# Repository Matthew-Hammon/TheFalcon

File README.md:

# The Falcon

This is a project that was inspired by ZSA's Moonlander and Voyager split keyboards. I loved how they looked and with my move to a keyboard-driven workflow, I decided that I needed to make the move. I started second-guessing myself when I saw the price, as I was a student, and I came to the realisation that I had the skills to design one.

## Features
* 36 keys per split
* Serial communication between keyboards
* USB2.0 with USB-C connectors
* Voltage protection for hot plugging
* 4 layer PCB
* RGB lighting (see the note)
* QMK compatible
* Compatible with both [Gateron Low Profile 2.0](https://www.gateron.co/products/gateron-low-profile-mechanical-switch-set) (KS-33) and [Gateron G Pro switches](https://www.gateron.co/products/gateron-switch-set)

> [!NOTE]
> I have not been able to get the RGB lighting to work. I have checked the PCB schematic and nothing stands out as the error but I could be wrong. I believe that the problem comes down to the firmware implementation and drivers.

### PCB
The PCB folder contains files for the left and right PCBs separately as well as a panelised version that combines them. The PCBs were designed by me with inspiration from other similar projects. Although four layers increase the production cost, they were intentionally kept to ensure proper signal integrity and return paths, especially due to the fast switching of multiple lines for RGB, PWM and the USB differential pair.

### Case
The SolidWorks folder contains all of the CAD files that I made for the case/switch panel. 
The folders ending with _Threaded are for the initial case designs when I had initial ideas of having the case CNCed. They have threaded pillars used for screwing the bottom plate into the top, with the top also housing the keyboard switches. 
The folders with _ScrewHoles contain a full CAD design for the case, with a bottom case being used along with M2.5 screws and hex standoffs to attach to the switch panel. The switch panel was made using FR-4 and placed alongside the PCB order. Two versions of this were made, one for 'normal' switches and an adjusted one for low-profile switches.

### Parts
All of the parts can be found in the PartsList.xlsx file. The file is detailed and most of the parts have links to places I sourced them from at the time.
A bill of materials for the panel is found as 'bom.xlsx' with the parts positions in 'pos.xlsx'. These were formatted for JLCPCB and at the time they worked. I take no responsibility for anyone who uses them along with the panel for production and I HIGHLY encourage anyone using the files to double-check everything.

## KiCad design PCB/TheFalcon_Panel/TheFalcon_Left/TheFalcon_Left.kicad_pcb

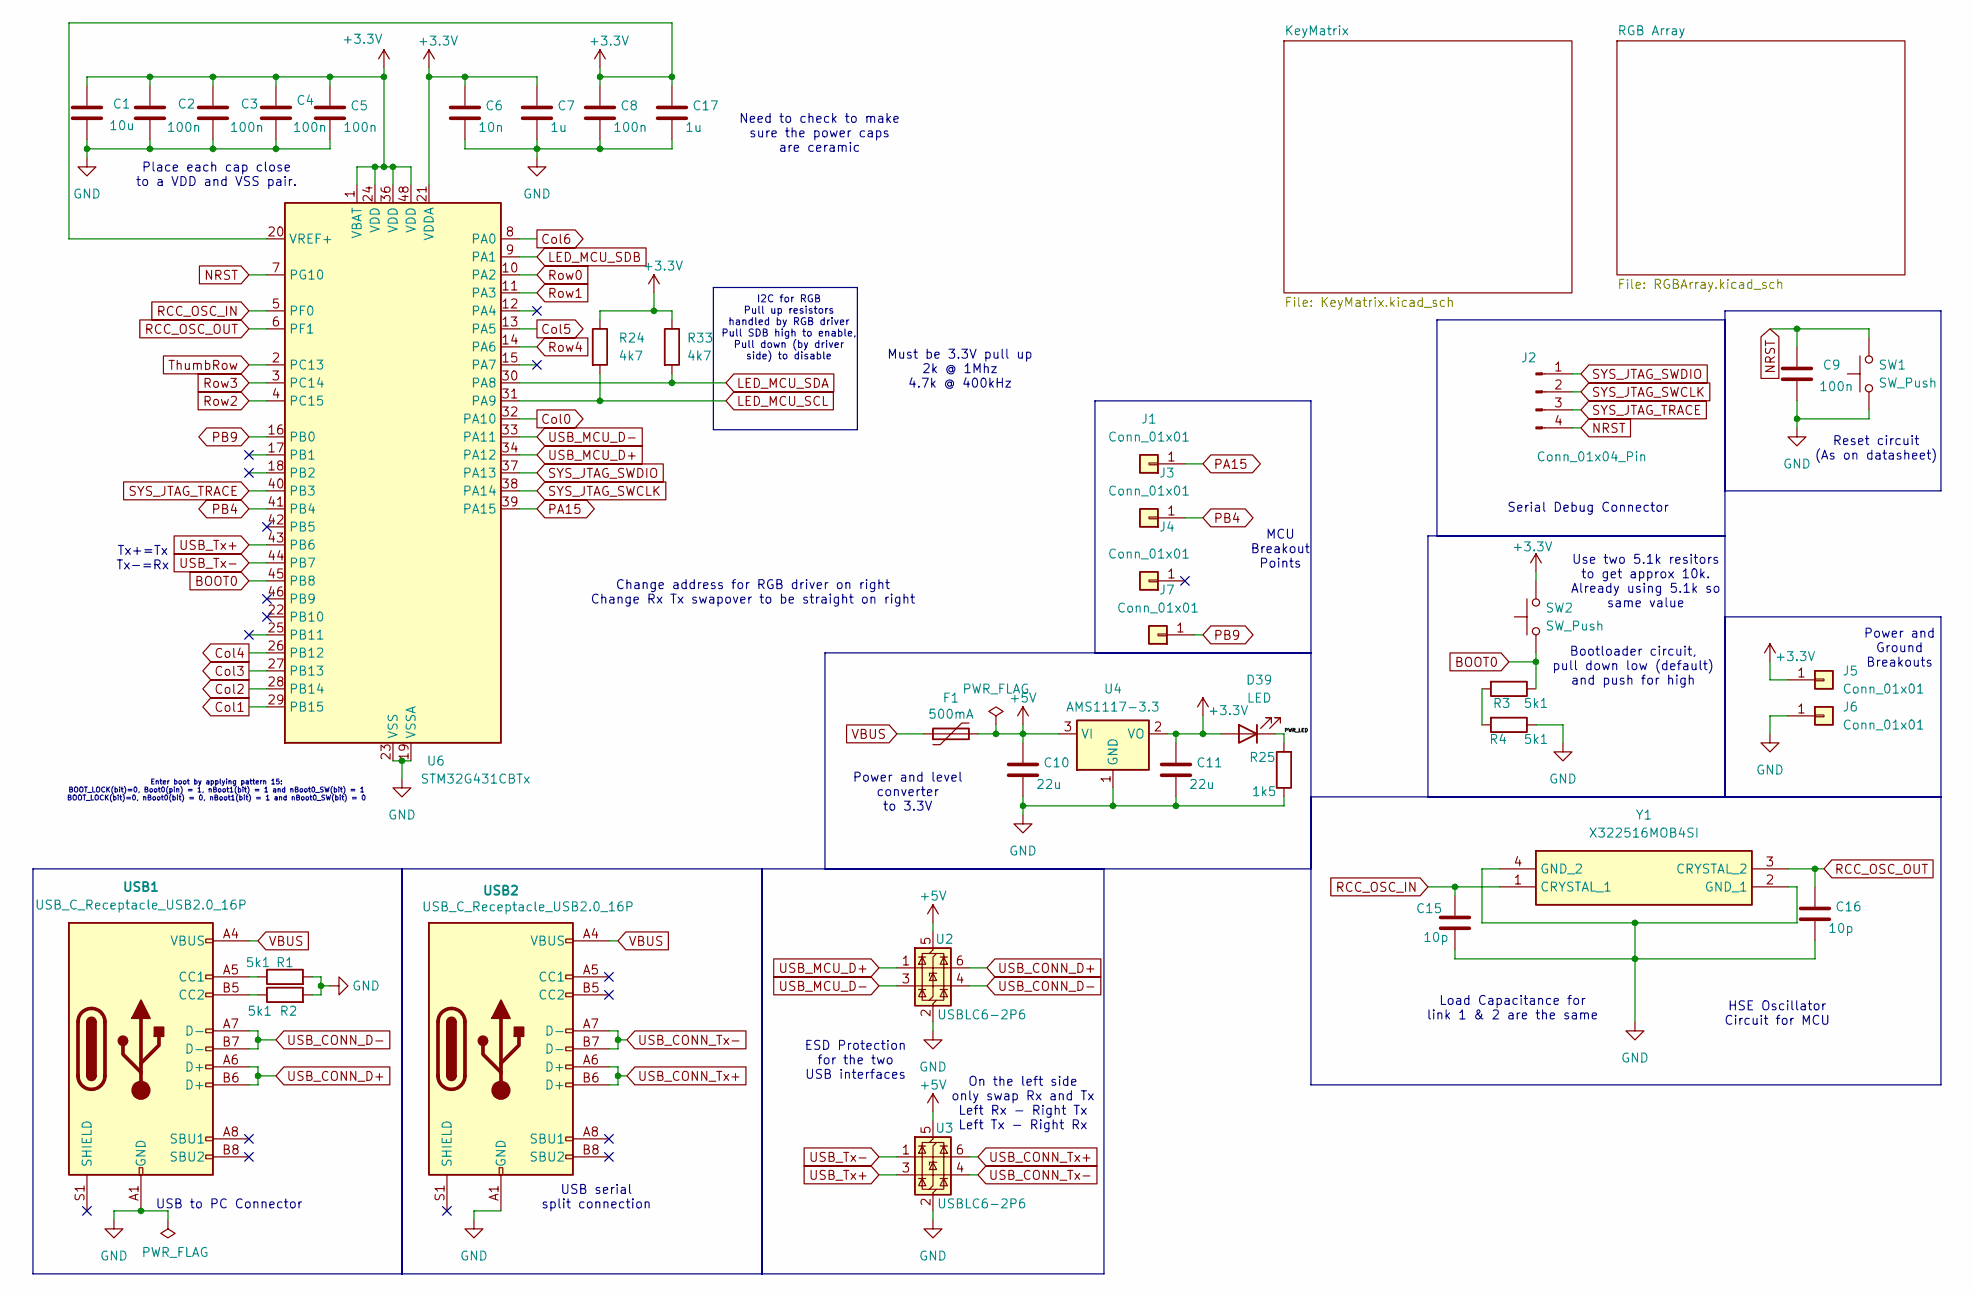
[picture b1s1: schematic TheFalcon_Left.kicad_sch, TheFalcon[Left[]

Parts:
C1: 10u; C_0805_2012Metric; LCSC Part Number C1713
C2, C3, C4, C5, C8, C9: 100n; C_0402_1005Metric; LCSC Part Number C1525
C6: 10n; C_0402_1005Metric; LCSC Part Number C1524
C7, C17: 1u; C_0603_1608Metric; LCSC Part Number C1592
C10, C11: 22u; C_1206_3216Metric; LCSC Part Number C1859
C15, C16: 10p; C_0402_1005Metric; LCSC Part Number C1545
D39: LED; LED_0805_2012Metric; LCSC Part Number C84260
F1: 500mA; Fuse_1206_3216Metric; LCSC Part Number C135336
J1, J3, J4, J5, J6, J7: Conn_01x01; SolderWire-0.1sqmm_1x01_D0.4mm_OD1mm
J2: Conn_01x04_Pin; SolderWire-1sqmm_1x04_P5.4mm_D1.4mm_OD2.7mm
R1, R2, R3, R4: 5k1; R_0603_1608Metric; LCSC Part Number C23067
R24, R33: 4k7; R_0603_1608Metric; LCSC Part Number C23162
R25: 1k5; R_0603_1608Metric; LCSC Part Number C22843
SW1, SW2: SW_Push; SPDT_Switch_KiCad_BasicComponent; LCSC Part Number C231329
U2, U3: USBLC6-2P6; SOT-666; LCSC Part Number C29780639
U4: AMS1117-3.3; SOT-223-3_TabPin2; LCSC Part Number C6186
U6: STM32G431CBTx; LQFP-48_7x7mm_P0.5mm; LCSC Part Number C529355
USB1, USB2: USB_C_Receptacle_USB2.0_16P; USB_C_Receptacle_G-Switch_GT-USB-7010ASV; LCSC Part Number C2988369
Y1: X322516MOB4SI; LCSC Part Number C12668

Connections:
+3.3V: C1.1, C2.1, C3.1, C4.1, C5.1, C6.1, C7.1, C8.1, C11.1, C17.1, D39.2 (A), J5.1, R24.1, R33.1, SW2.2, U4.2 (VO), U6.1 (VBAT), U6.20 (VREF+), U6.21 (VDDA), U6.24 (VDD), U6.36 (VDD), U6.48 (VDD)
+5V: C10.1, F1.2, U2.5 (VBUS), U3.5 (VBUS), U4.3 (VI); also elsewhere on the board
/PWR_LED: D39.1 (K), R25.2
BOOT0: R3.1, SW2.1, U6.45 (PB8)
Col0: U6.32 (PA10); also elsewhere on the board
Col1: U6.29 (PB15); also elsewhere on the board
Col2: U6.28 (PB14); also elsewhere on the board
Col3: U6.27 (PB13); also elsewhere on the board
Col4: U6.26 (PB12); also elsewhere on the board
Col5: U6.13 (PA5); also elsewhere on the board
Col6: U6.8 (PA0); also elsewhere on the board
GND: C1.2, C2.2, C3.2, C4.2, C5.2, C6.2, C7.2, C8.2, C9.2, C10.2, C11.2, C15.2, C16.2, C17.2, J6.1, R1.2, R2.2, R4.1, R25.1, SW1.1, U2.2 (GND), U3.2 (GND), U4.1 (GND), U6.19 (VSSA), U6.23 (VSS), U6.35 (VSS), U6.47 (VSS), USB1.A1 (GND), USB1.A12 (GND), USB1.B1 (GND), USB1.B12 (GND), USB2.A1 (GND), USB2.A12 (GND), USB2.B1 (GND), USB2.B12 (GND), Y1.2 (GND_1), Y1.4 (GND_2); also elsewhere on the board
LED_MCU_SCL: R24.2, U6.31 (PA9); also elsewhere on the board
LED_MCU_SDA: R33.2, U6.30 (PA8); also elsewhere on the board
LED_MCU_SDB: U6.9 (PA1); also elsewhere on the board
NRST: C9.1, J2.4, SW1.2, U6.7 (PG10)
unnamed: R3.2, R4.2
unnamed: R1.1, USB1.A5 (CC1)
unnamed: R2.1, USB1.B5 (CC2)
PA15: J1.1, U6.39 (PA15)
PB4: J3.1, U6.41 (PB4)
PB9: J7.1, U6.16 (PB0)
RCC_OSC_IN: C15.1, U6.5 (PF0), Y1.1 (CRYSTAL_1)
RCC_OSC_OUT: C16.1, U6.6 (PF1), Y1.3 (CRYSTAL_2)
Row0: U6.10 (PA2); also elsewhere on the board
Row1: U6.11 (PA3); also elsewhere on the board
Row2: U6.4 (PC15); also elsewhere on the board
Row3: U6.3 (PC14); also elsewhere on the board
Row4: U6.14 (PA6); also elsewhere on the board
SYS_JTAG_SWCLK: J2.2, U6.38 (PA14)
SYS_JTAG_SWDIO: J2.1, U6.37 (PA13)
SYS_JTAG_TRACE: J2.3, U6.40 (PB3)
ThumbRow: U6.2 (PC13); also elsewhere on the board
USB_CONN_D+: U2.6 (I/O1), USB1.A6 (D+), USB1.B6 (D+)
USB_CONN_D-: U2.4 (I/O2), USB1.A7 (D-), USB1.B7 (D-)
USB_CONN_Tx+: U3.6 (I/O1), USB2.A6 (D+), USB2.B6 (D+)
USB_CONN_Tx-: U3.4 (I/O2), USB2.A7 (D-), USB2.B7 (D-)
USB_MCU_D+: U2.1 (I/O1), U6.34 (PA12)
USB_MCU_D-: U2.3 (I/O2), U6.33 (PA11)
USB_Tx+: U3.3 (I/O2), U6.43 (PB6)
USB_Tx-: U3.1 (I/O1), U6.44 (PB7)
VBUS: F1.1, USB1.A4 (VBUS), USB1.A9 (VBUS), USB1.B4 (VBUS), USB1.B9 (VBUS), USB2.A4 (VBUS), USB2.A9 (VBUS), USB2.B4 (VBUS), USB2.B9 (VBUS)

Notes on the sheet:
Place each cap close to a VDD and VSS pair.
Load Capacitance for link 1 & 2 are the same
Power and Ground Breakouts
Tx+=Tx Tx-=Rx
Must be 3.3V pull up 2k @ 1Mhz 4.7k @ 400kHz
Need to check to make sure the power caps are ceramic
Reset circuit (As on datasheet)
USB serial split connection
Bootloader circuit, pull down low (default) and push for high
Change address for RGB driver on right Change Rx Tx swapover to be straight on right
Enter boot by applying pattern 15: BOOT_LOCK(bit)=0, Boot0(pin) = 1, nBoot1(bit) = 1 and nBoot0_SW(bit) = 1 BOOT_LOCK(bit)=0, nBoot0(bit) = 0, nBoot1(bit) = 1 and nBoot0_SW(bit) = 0
Power and level converter to 3.3V
MCU Breakout Points
USB to PC Connector
ESD Protection for the two USB interfaces
HSE Oscillator Circuit for MCU
I2C for RGB Pull up resistors handled by RGB driver Pull SDB high to enable, Pull down (by driver side) to disable
Use two 5.1k resitors to get approx 10k. Already using 5.1k so same value
Serial Debug Connector
On the left side only swap Rx and Tx Left Rx - Right Tx Left Tx - Right Rx

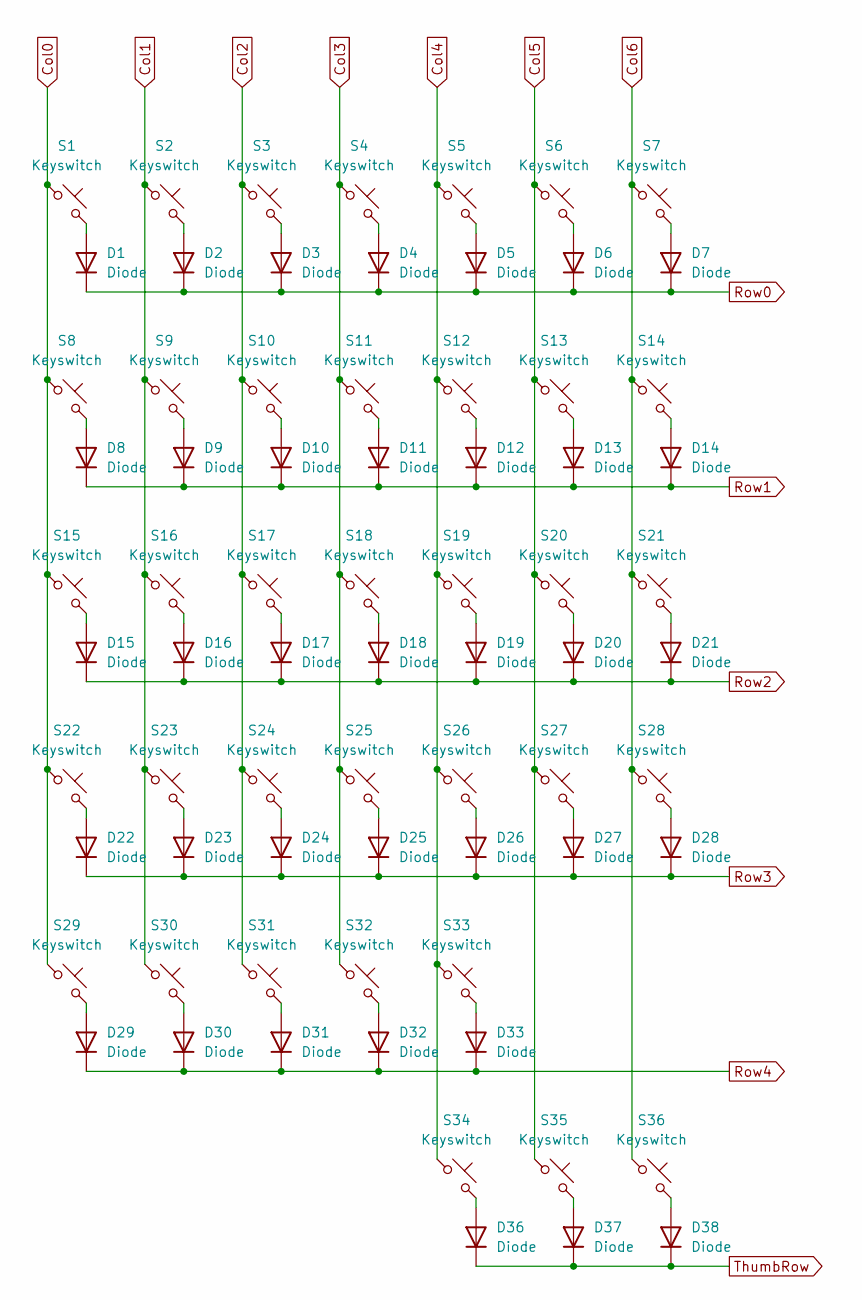
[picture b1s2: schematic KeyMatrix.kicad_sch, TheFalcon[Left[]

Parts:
D1, D2, D3, D4, D5, D6, D7, D8, D9, D10, D11, D12, D13, D14, D15, D16, D17, D18, D19, D20, D21, D22, D23, D24, D25, D26, D27, D28, D29, D30, D31, D32, D33, D36, D37, D38: Diode; D_SOD-123; LCSC Part Number C2099
S1, S2, S3, S4, S5, S6, S7, S8, S9, S10, S11, S12, S13, S14, S15, S16, S17, S18, S19, S20, S21, S22, S23, S24, S25, S26, S27, S28, S29, S30, S31, S32, S33, S34: Keyswitch; MX_KS33-Solderable-1U
S35, S36: Keyswitch; MX_KS33-Solderable-1.5U-Vertical

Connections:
Col0: S1.1, S8.1, S15.1, S22.1, S29.1; also elsewhere on the board
Col1: S2.1, S9.1, S16.1, S23.1, S30.1; also elsewhere on the board
Col2: S3.1, S10.1, S17.1, S24.1, S31.1; also elsewhere on the board
Col3: S4.1, S11.1, S18.1, S25.1, S32.1; also elsewhere on the board
Col4: S5.1, S12.1, S19.1, S26.1, S33.1, S34.1; also elsewhere on the board
Col5: S6.1, S13.1, S20.1, S27.1, S35.1; also elsewhere on the board
Col6: S7.1, S14.1, S21.1, S28.1, S36.1; also elsewhere on the board
unnamed: D1.2 (A), S1.2
unnamed: D2.2 (A), S2.2
unnamed: D3.2 (A), S3.2
unnamed: D4.2 (A), S4.2
unnamed: D5.2 (A), S5.2
unnamed: D6.2 (A), S6.2
unnamed: D7.2 (A), S7.2
unnamed: D8.2 (A), S8.2
unnamed: D9.2 (A), S9.2
unnamed: D10.2 (A), S10.2
unnamed: D11.2 (A), S11.2
unnamed: D12.2 (A), S12.2
unnamed: D13.2 (A), S13.2
unnamed: D14.2 (A), S14.2
unnamed: D15.2 (A), S15.2
unnamed: D16.2 (A), S16.2
unnamed: D17.2 (A), S17.2
unnamed: D18.2 (A), S18.2
unnamed: D19.2 (A), S19.2
unnamed: D20.2 (A), S20.2
unnamed: D21.2 (A), S21.2
unnamed: D22.2 (A), S22.2
unnamed: D23.2 (A), S23.2
unnamed: D24.2 (A), S24.2
unnamed: D25.2 (A), S25.2
unnamed: D26.2 (A), S26.2
unnamed: D27.2 (A), S27.2
unnamed: D28.2 (A), S28.2
unnamed: D29.2 (A), S29.2
unnamed: D30.2 (A), S30.2
unnamed: D31.2 (A), S31.2
unnamed: D32.2 (A), S32.2
unnamed: D33.2 (A), S33.2
unnamed: D36.2 (A), S34.2
unnamed: D37.2 (A), S35.2
unnamed: D38.2 (A), S36.2
Row0: D1.1 (K), D2.1 (K), D3.1 (K), D4.1 (K), D5.1 (K), D6.1 (K), D7.1 (K); also elsewhere on the board
Row1: D8.1 (K), D9.1 (K), D10.1 (K), D11.1 (K), D12.1 (K), D13.1 (K), D14.1 (K); also elsewhere on the board
Row2: D15.1 (K), D16.1 (K), D17.1 (K), D18.1 (K), D19.1 (K), D20.1 (K), D21.1 (K); also elsewhere on the board
Row3: D22.1 (K), D23.1 (K), D24.1 (K), D25.1 (K), D26.1 (K), D27.1 (K), D28.1 (K); also elsewhere on the board
Row4: D29.1 (K), D30.1 (K), D31.1 (K), D32.1 (K), D33.1 (K); also elsewhere on the board
ThumbRow: D36.1 (K), D37.1 (K), D38.1 (K); also elsewhere on the board

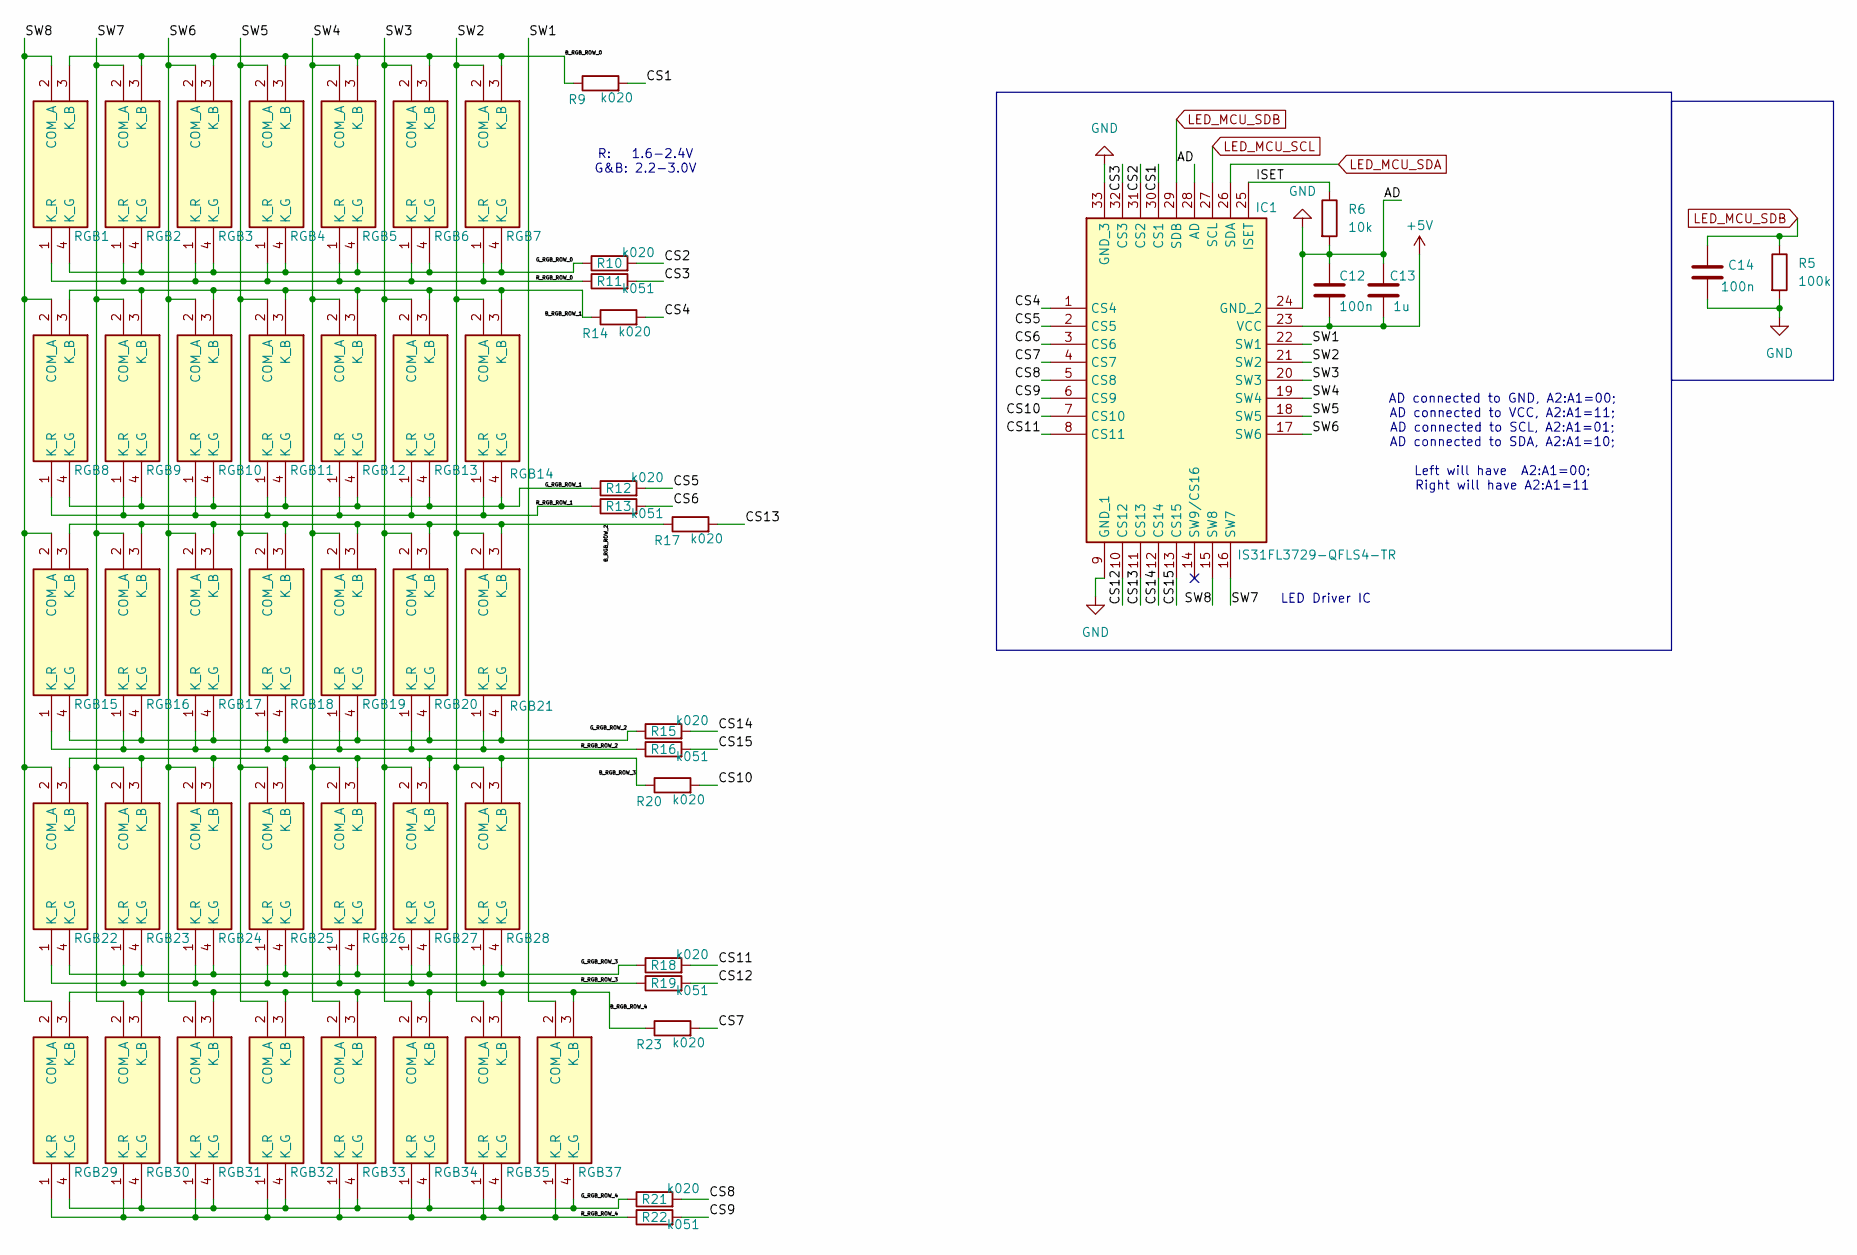
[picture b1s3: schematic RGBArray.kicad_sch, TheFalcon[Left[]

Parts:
C12, C14: 100n; C_0402_1005Metric; LCSC Part Number C1525
C13: 1u; C_0603_1608Metric; LCSC Part Number C1592
IC1: IS31FL3729-QFLS4-TR; QFN40P400X400X80-33N-D; LCSC Part Number C2940549
R5: 100k; R_0603_1608Metric; LCSC Part Number C14675
R6: 10k; R_0603_1608Metric; LCSC Part Number C15401
R9, R10, R12, R14, R15, R17, R18, R20, R21, R23: k020; R_0603_1608Metric; LCSC Part Number C22950
R11, R13, R16, R19, R22: k051; R_0603_1608Metric; LCSC Part Number C17738
RGB1, RGB2, RGB3, RGB4, RGB5, RGB6, RGB7, RGB8, RGB9, RGB10, RGB11, RGB12, RGB13, RGB14, RGB15, RGB16, RGB17, RGB18, RGB19, RGB20, RGB21, RGB22, RGB23, RGB24, RGB25, RGB26, RGB27, RGB28, RGB29, RGB30, RGB31, RGB32, RGB33, RGB34, RGB35, RGB37: T36K3BGR-05D000121U1930; T36K3BGR05D000121U1930_MODEL_INVERTED

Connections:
+5V: C12.2, C13.2, IC1.23 (VCC); also elsewhere on the board
/RGB Array/B_RGB_ROW_0: R9.1, RGB1.3 (K_B), RGB2.3 (K_B), RGB3.3 (K_B), RGB4.3 (K_B), RGB5.3 (K_B), RGB6.3 (K_B), RGB7.3 (K_B)
/RGB Array/B_RGB_ROW_1: R14.1, RGB8.3 (K_B), RGB9.3 (K_B), RGB10.3 (K_B), RGB11.3 (K_B), RGB12.3 (K_B), RGB13.3 (K_B), RGB14.3 (K_B)
/RGB Array/B_RGB_ROW_2: R17.1, RGB15.3 (K_B), RGB16.3 (K_B), RGB17.3 (K_B), RGB18.3 (K_B), RGB19.3 (K_B), RGB20.3 (K_B), RGB21.3 (K_B)
/RGB Array/B_RGB_ROW_3: R20.1, RGB22.3 (K_B), RGB23.3 (K_B), RGB24.3 (K_B), RGB25.3 (K_B), RGB26.3 (K_B), RGB27.3 (K_B), RGB28.3 (K_B)
/RGB Array/B_RGB_ROW_4: R23.1, RGB29.3 (K_B), RGB30.3 (K_B), RGB31.3 (K_B), RGB32.3 (K_B), RGB33.3 (K_B), RGB34.3 (K_B), RGB35.3 (K_B), RGB37.3 (K_B)
/RGB Array/CS1: IC1.30 (CS1), R9.2
/RGB Array/CS2: IC1.31 (CS2), R10.2
/RGB Array/CS3: IC1.32 (CS3), R11.2
/RGB Array/CS4: IC1.1 (CS4), R14.2
/RGB Array/CS5: IC1.2 (CS5), R12.2
/RGB Array/CS6: IC1.3 (CS6), R13.2
/RGB Array/CS7: IC1.4 (CS7), R23.2
/RGB Array/CS8: IC1.5 (CS8), R21.2
/RGB Array/CS9: IC1.6 (CS9), R22.2
/RGB Array/CS10: IC1.7 (CS10), R20.2
/RGB Array/CS11: IC1.8 (CS11), R18.2
/RGB Array/CS12: IC1.10 (CS12), R19.2
/RGB Array/CS13: IC1.11 (CS13), R17.2
/RGB Array/CS14: IC1.12 (CS14), R15.2
/RGB Array/CS15: IC1.13 (CS15), R16.2
/RGB Array/G_RGB_ROW_0: R10.1, RGB1.4 (K_G), RGB2.4 (K_G), RGB3.4 (K_G), RGB4.4 (K_G), RGB5.4 (K_G), RGB6.4 (K_G), RGB7.4 (K_G)
/RGB Array/G_RGB_ROW_1: R12.1, RGB8.4 (K_G), RGB9.4 (K_G), RGB10.4 (K_G), RGB11.4 (K_G), RGB12.4 (K_G), RGB13.4 (K_G), RGB14.4 (K_G)
/RGB Array/G_RGB_ROW_2: R15.1, RGB15.4 (K_G), RGB16.4 (K_G), RGB17.4 (K_G), RGB18.4 (K_G), RGB19.4 (K_G), RGB20.4 (K_G), RGB21.4 (K_G)
/RGB Array/G_RGB_ROW_3: R18.1, RGB22.4 (K_G), RGB23.4 (K_G), RGB24.4 (K_G), RGB25.4 (K_G), RGB26.4 (K_G), RGB27.4 (K_G), RGB28.4 (K_G)
/RGB Array/G_RGB_ROW_4: R21.1, RGB29.4 (K_G), RGB30.4 (K_G), RGB31.4 (K_G), RGB32.4 (K_G), RGB33.4 (K_G), RGB34.4 (K_G), RGB35.4 (K_G), RGB37.4 (K_G)
/RGB Array/ISET: IC1.25 (ISET), R6.1
/RGB Array/R_RGB_ROW_0: R11.1, RGB1.1 (K_R), RGB2.1 (K_R), RGB3.1 (K_R), RGB4.1 (K_R), RGB5.1 (K_R), RGB6.1 (K_R), RGB7.1 (K_R)
/RGB Array/R_RGB_ROW_1: R13.1, RGB8.1 (K_R), RGB9.1 (K_R), RGB10.1 (K_R), RGB11.1 (K_R), RGB12.1 (K_R), RGB13.1 (K_R), RGB14.1 (K_R)
/RGB Array/R_RGB_ROW_2: R16.1, RGB15.1 (K_R), RGB16.1 (K_R), RGB17.1 (K_R), RGB18.1 (K_R), RGB19.1 (K_R), RGB20.1 (K_R), RGB21.1 (K_R)
/RGB Array/R_RGB_ROW_3: R19.1, RGB22.1 (K_R), RGB23.1 (K_R), RGB24.1 (K_R), RGB25.1 (K_R), RGB26.1 (K_R), RGB27.1 (K_R), RGB28.1 (K_R)
/RGB Array/R_RGB_ROW_4: R22.1, RGB29.1 (K_R), RGB30.1 (K_R), RGB31.1 (K_R), RGB32.1 (K_R), RGB33.1 (K_R), RGB34.1 (K_R), RGB35.1 (K_R), RGB37.1 (K_R)
/RGB Array/SW1: IC1.22 (SW1), RGB37.2 (COM_A)
/RGB Array/SW2: IC1.21 (SW2), RGB7.2 (COM_A), RGB14.2 (COM_A), RGB21.2 (COM_A), RGB28.2 (COM_A), RGB35.2 (COM_A)
/RGB Array/SW3: IC1.20 (SW3), RGB6.2 (COM_A), RGB13.2 (COM_A), RGB20.2 (COM_A), RGB27.2 (COM_A), RGB34.2 (COM_A)
/RGB Array/SW4: IC1.19 (SW4), RGB5.2 (COM_A), RGB12.2 (COM_A), RGB19.2 (COM_A), RGB26.2 (COM_A), RGB33.2 (COM_A)
/RGB Array/SW5: IC1.18 (SW5), RGB4.2 (COM_A), RGB11.2 (COM_A), RGB18.2 (COM_A), RGB25.2 (COM_A), RGB32.2 (COM_A)
/RGB Array/SW6: IC1.17 (SW6), RGB3.2 (COM_A), RGB10.2 (COM_A), RGB17.2 (COM_A), RGB24.2 (COM_A), RGB31.2 (COM_A)
/RGB Array/SW7: IC1.16 (SW7), RGB2.2 (COM_A), RGB9.2 (COM_A), RGB16.2 (COM_A), RGB23.2 (COM_A), RGB30.2 (COM_A)
/RGB Array/SW8: IC1.15 (SW8), RGB1.2 (COM_A), RGB8.2 (COM_A), RGB15.2 (COM_A), RGB22.2 (COM_A), RGB29.2 (COM_A)
GND: C12.1, C13.1, C14.2, IC1.9 (GND_1), IC1.24 (GND_2), IC1.28 (AD), IC1.33 (GND_3), R5.2, R6.2; also elsewhere on the board
LED_MCU_SCL: IC1.27 (SCL); also elsewhere on the board
LED_MCU_SDA: IC1.26 (SDA); also elsewhere on the board
LED_MCU_SDB: C14.1, IC1.29 (SDB), R5.1; also elsewhere on the board

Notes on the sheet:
AD connected to GND, A2:A1=00; AD connected to VCC, A2:A1=11; AD connected to SCL, A2:A1=01; AD connected to SDA, A2:A1=10; Left will have A2:A1=00; Right will have A2:A1=11
R: 1.6-2.4V G&B: 2.2-3.0V
LED Driver IC

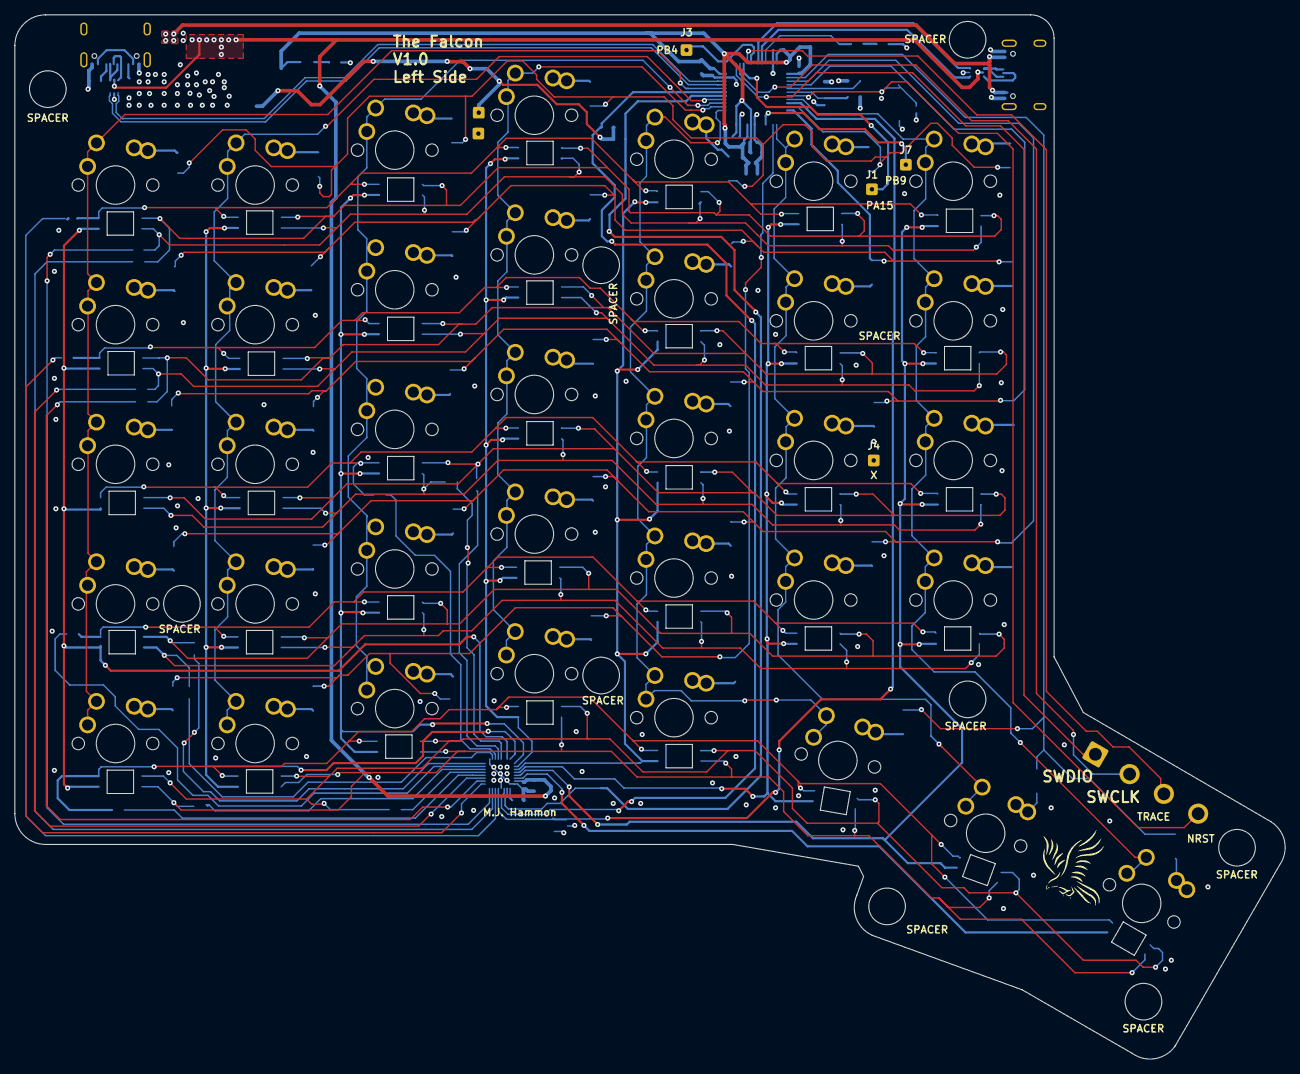
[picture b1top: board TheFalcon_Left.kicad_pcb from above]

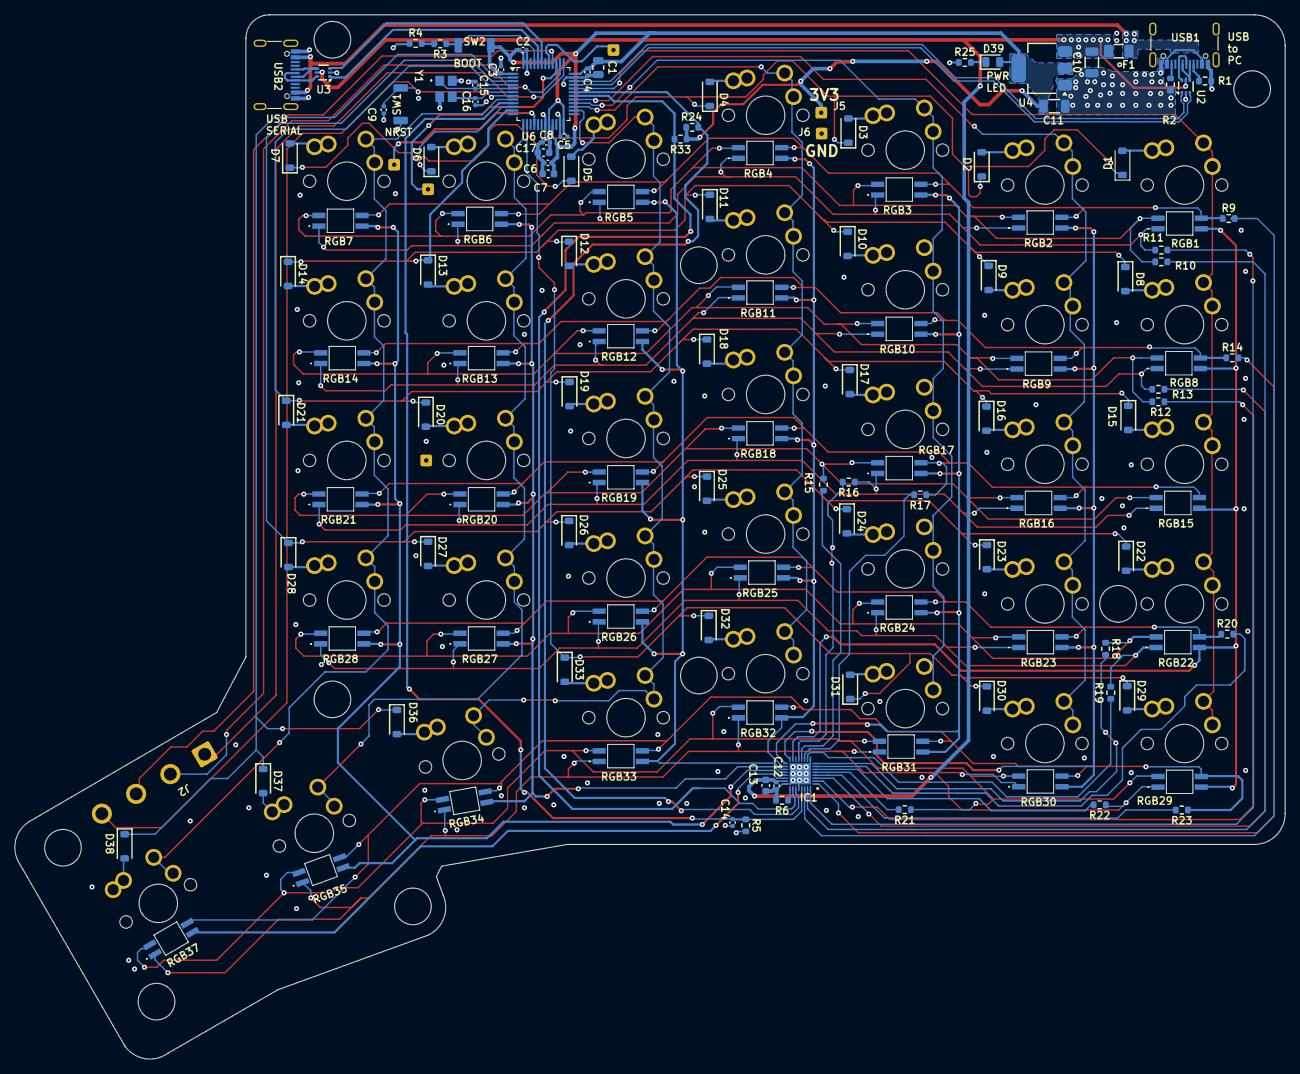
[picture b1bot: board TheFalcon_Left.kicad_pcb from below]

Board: 4 copper layers, 173.3 x 142.5 mm, 168 parts (92 on the bottom side), 117 nets.

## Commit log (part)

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2025-06-29 Save
2025-07-08 save, about to slim
2025-07-12 Saving before I go crazy on PCB
2025-07-14 TwoUSBs on Top
2025-07-19 Cleaning up
    I have all connections, just cleaning up
2025-07-19 Save
    Done left side, going to start right side now
2025-07-21 Right Side Done
    Need to check but right side looks good
2025-07-29 Going to add screw holes
2025-07-29 Saving
    Added Edge but about to get rid of screws on edge
2025-07-30 Save
    Case done for left and right side
2025-07-31 Save
    Checked right PCB and hole to track spacing for left. Will do check for left pcb tomorrow
2025-08-01 Save
    Done checking left and right PCB and case.
2025-08-03 Files ready for production
    Going to panelise seperate files to reduce PCBA cost
2025-08-04 Adding Panels to PCB
2025-08-06 Save
    Trying a different panel
